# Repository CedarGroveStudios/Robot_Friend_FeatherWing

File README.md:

# Cedar Grove Robot Friend FeatherWing

### _A passive FeatherWing adapter for stacking an Adafruit PyBadge or PyGamer onto a Crickit FeatherWing. Includes a prototyping area for custom circuitry and sensors._

Perched on the top of a robot chassis, the Cedar Grove Robot Friend FeatherWing passively connects the FeatherWing connections of a PyBadge or PyGamer device with a Crickit FeatherWing. The Crickit provides 3.3V power to the attached PyBadge/PyGamer. All Feather signals are interconnected to accommodate custom alterations to the Crickit module, such as support for IRQ/Busy or sensor modifications.

The Cedar Grove Robot Friend includes a prototype area and a breakout of all Feather pins for further cusomization.

For use ONLY with the Crickit FeatherWing and compatible Feather MCU boards. To date, it has only been tested with the PyGamer and PyBadge. Double-check pin compatibility if you plan to attach or stack other Feather devices.

#### Caution:
The Crickit is capable of providing up to 150mA of 3.3-volt power to the attached PB/PG Feather. In normal operation without any of the NeoPixels lighted or the use of the built-in speaker amplifier, the PB/PG will draw about 60mA from the Crickit's internal 3.3-volt regulator. 

When the PB/PG is powered only by the Crickit via the Feather 3V pin, the PB/PG 3.3v regulator is reverse-biased by the Crickit-supplied +3.3 volts. The AP2112-3.3 regulator has an intrinsic MOSFET diode between its output and input that conducts when reverse-biased, raising the voltage of the input pin to the same as the output pin less the forward voltage drop of the diode. What that means is that 5-volt components like the PB/PG's NeoPixels and Stemma connectors will have approximately +3.2 volts available for operation. The PB/PG NeoPixels seem to work with the lower voltage, but might not be 100% reliable. 

Since the reverse-biased "feature" of the PB/PG's internal regulator is not documented in the datasheet, it's probably a good idea to limit use of the PB/PG NeoPixels when stacked on the Crickit via the Robot Friend FeatherWing. If you need to brightly light the PB/PG NeoPixels or connect a speaker to the on-board amplifier, consider adding a small LiPo battery directly to the PB/PG or just use the Crickit's on-board NeoPixel or drive a string via the Crickit's external NeoPixel connector. If a louder speaker is needed, use the Crickit's speaker output since the Crickit amplifier is not connected to the 3.3-volt power supply.

Intrinsic MOSFET Diode Discussion: https://www.digikey.com/en/articles/techzone/2016/sep/the-significance-of-the-intrinsic-body-diodes-inside-mosfets

OSH Park project: <a href="https://oshpark.com/shared_projects/N1lNaemv"></img></a>

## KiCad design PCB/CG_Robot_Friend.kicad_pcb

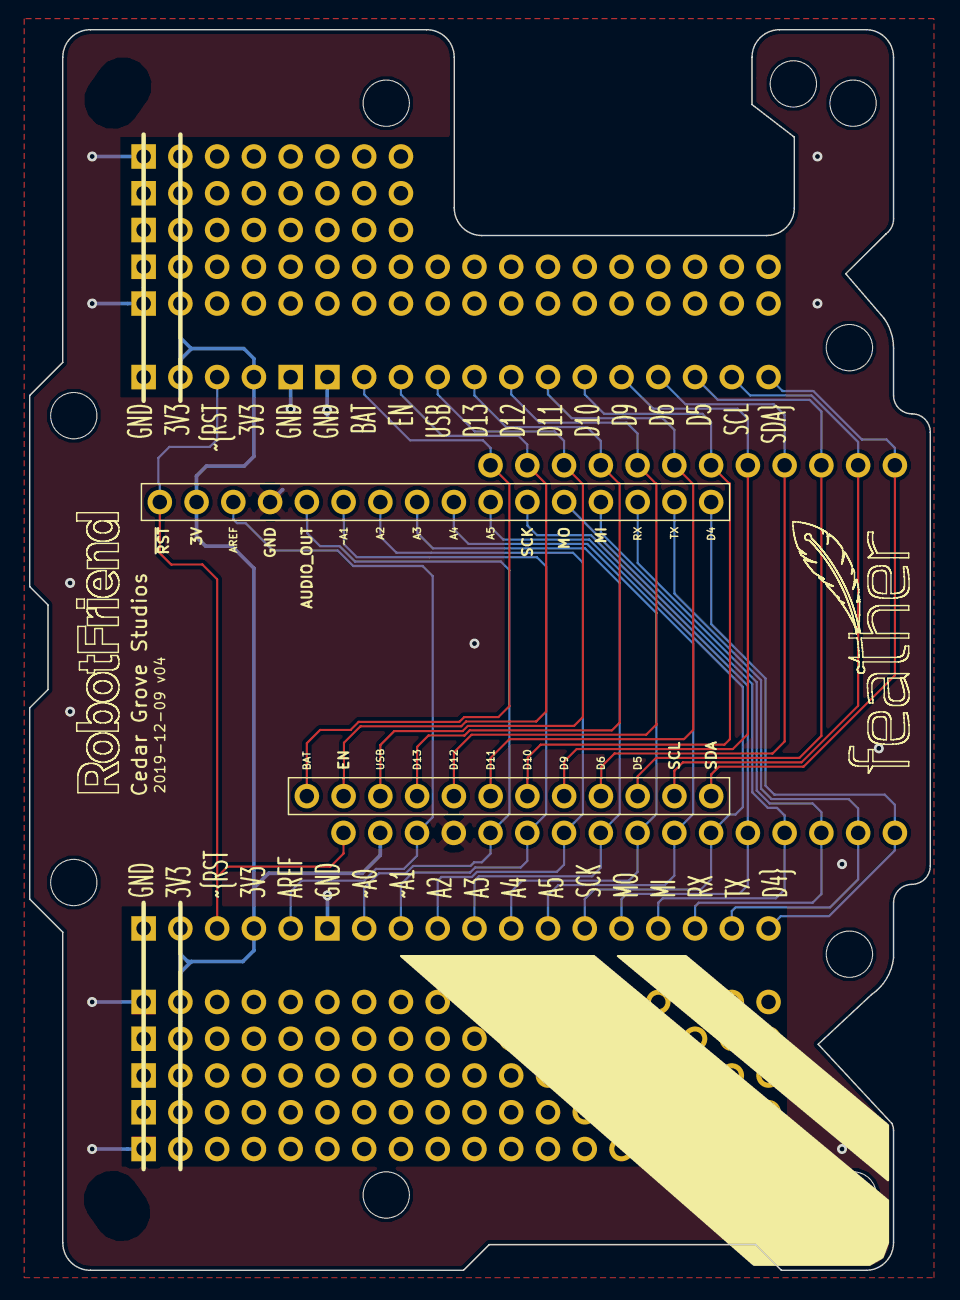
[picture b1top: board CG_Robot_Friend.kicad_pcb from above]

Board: 2 copper layers, 62.2 x 85.7 mm, 14 parts (1 on the bottom side), 28 nets.

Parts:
J1, J2, J3, J4, J5, J6, J7, J8, J9: PROTO; Pin_Header_Straight_1x18_Pitch2.54mm_nosilk
J10, J11, J12: PROTO; Pin_Header_Straight_1x08_Pitch2.54mm_no_silk
M1: PyBadge_PyGamer_Wing; Adafruit_PyBadge_PyGamer_Wing_conn_no_mounting_holes
M2: Crickit_FeatherWing; Adafruit_Crickit_Flip_no_mounting_holes

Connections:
/3V3: J1.2, J1.4, J2.2, J2.4, J3.2, J4.2, J5.2, J6.2, J7.2, J8.2, J9.2, J10.2, J11.2, J12.2, M1.2, M2.2
/A2: J1.9, M1.7, M2.7
/A3: J1.10, M1.8, M2.8
/A4: J1.11, M1.9, M2.9
/A5: J1.12, M1.10, M2.10
/AREF: J1.5, M1.3, M2.3
/AUDIO_OUT: J1.7, M1.5, M2.5
/BAT: J2.7, M1.17, M2.17
/D4: J1.18, M1.16, M2.16
/D5: J2.16, M1.26, M2.26
/D6: J2.15, M1.25, M2.25
/D9: J2.14, M1.24, M2.24
/D10: J2.13, M1.23, M2.23
/D11: J2.12, M1.22, M2.22
/D12: J2.11, M1.21, M2.21
/D13: J2.10, M1.20, M2.20
/ENABLE: J2.8, M1.18, M2.18
/MISO: J1.15, M1.13, M2.13
/MOSI: J1.14, M1.12, M2.12
/RX: J1.16, M1.14, M2.14
/SCL: J2.17, M1.27, M2.27
/SCLK: J1.13, M1.11, M2.11
/SDA: J2.18, M1.28, M2.28
/TX: J1.17, M1.15, M2.15
/USB: J2.9, M1.19, M2.19
/~RESET: J1.3, J2.3, M1.1, M2.1
/~~A1: J1.8, M1.6, M2.6
GND: J1.1, J1.6, J2.1, J2.5, J2.6, J3.1, J4.1, J5.1, J6.1, J7.1, J8.1, J9.1, J10.1, J11.1, J12.1, M1.4, M2.4

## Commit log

2019-11-11 initial repo load
2019-11-12 update to v03
2019-11-12 photos of prototype
2019-11-21 update mechanical PCB design
    to open up a few of the hidden Crickit connectors
2019-11-21 updated photos
2019-11-21 Update for PCB version 03
2019-11-30 include M0 HalloWing photo
2019-12-02 add Crickit pinout graphic
2019-12-04 update test code
2019-12-07 update simpletest
2019-12-08 update testing suite
2019-12-09 PyPanel_concept
2019-12-10 update panel abstraction and test code
2019-12-10 update to PCB v04: enhance cutout
2019-12-10 update to v04
2019-12-11 update tests and PyPanel library
2019-12-11 update test and pypanel library
2019-12-12 update docs
2019-12-13 add photo and updated crickit library (just until merged)
2019-12-14 develop auto-config scheme
2019-12-15 update for semi-auto "plug-n-play" configurator
2019-12-15 update device discovery code
2019-12-15 clarify a few variable names
2019-12-16 updated PCB layout for I/O connector
2019-12-18 add RTC wing to device catalog
2019-12-18 update oshpark link
2020-04-17 move pypanel to its own repo
2020-05-20 update supporting documentation
2020-11-09 update gitignore
2021-07-12 update documentation
2022-09-02 update license
